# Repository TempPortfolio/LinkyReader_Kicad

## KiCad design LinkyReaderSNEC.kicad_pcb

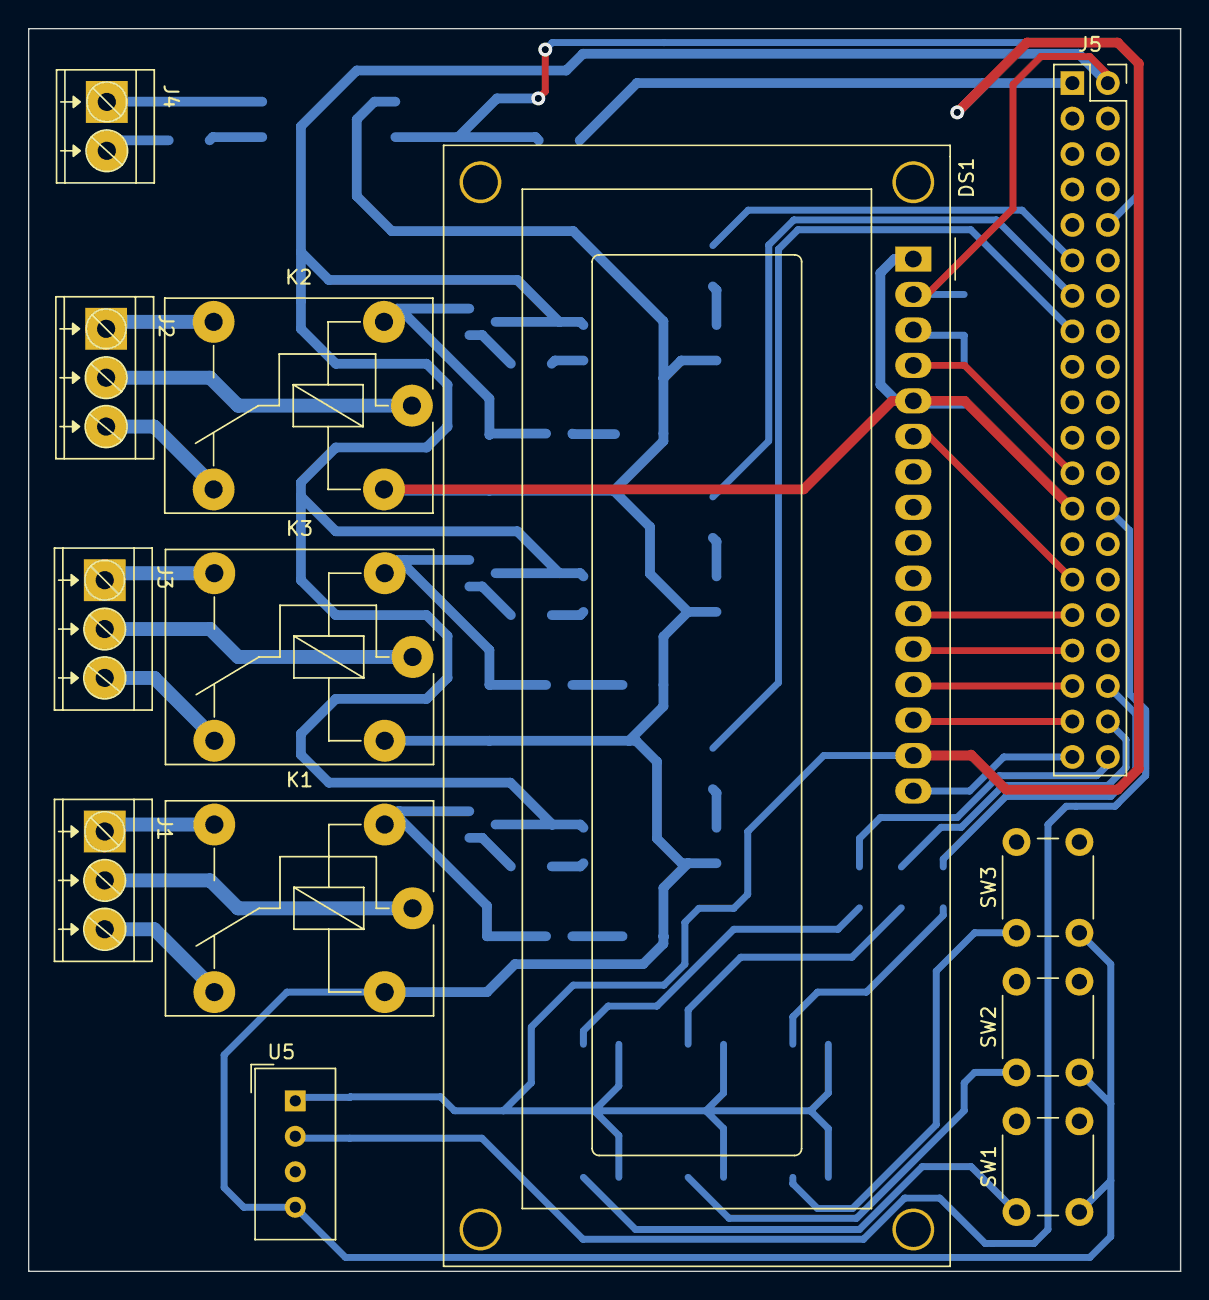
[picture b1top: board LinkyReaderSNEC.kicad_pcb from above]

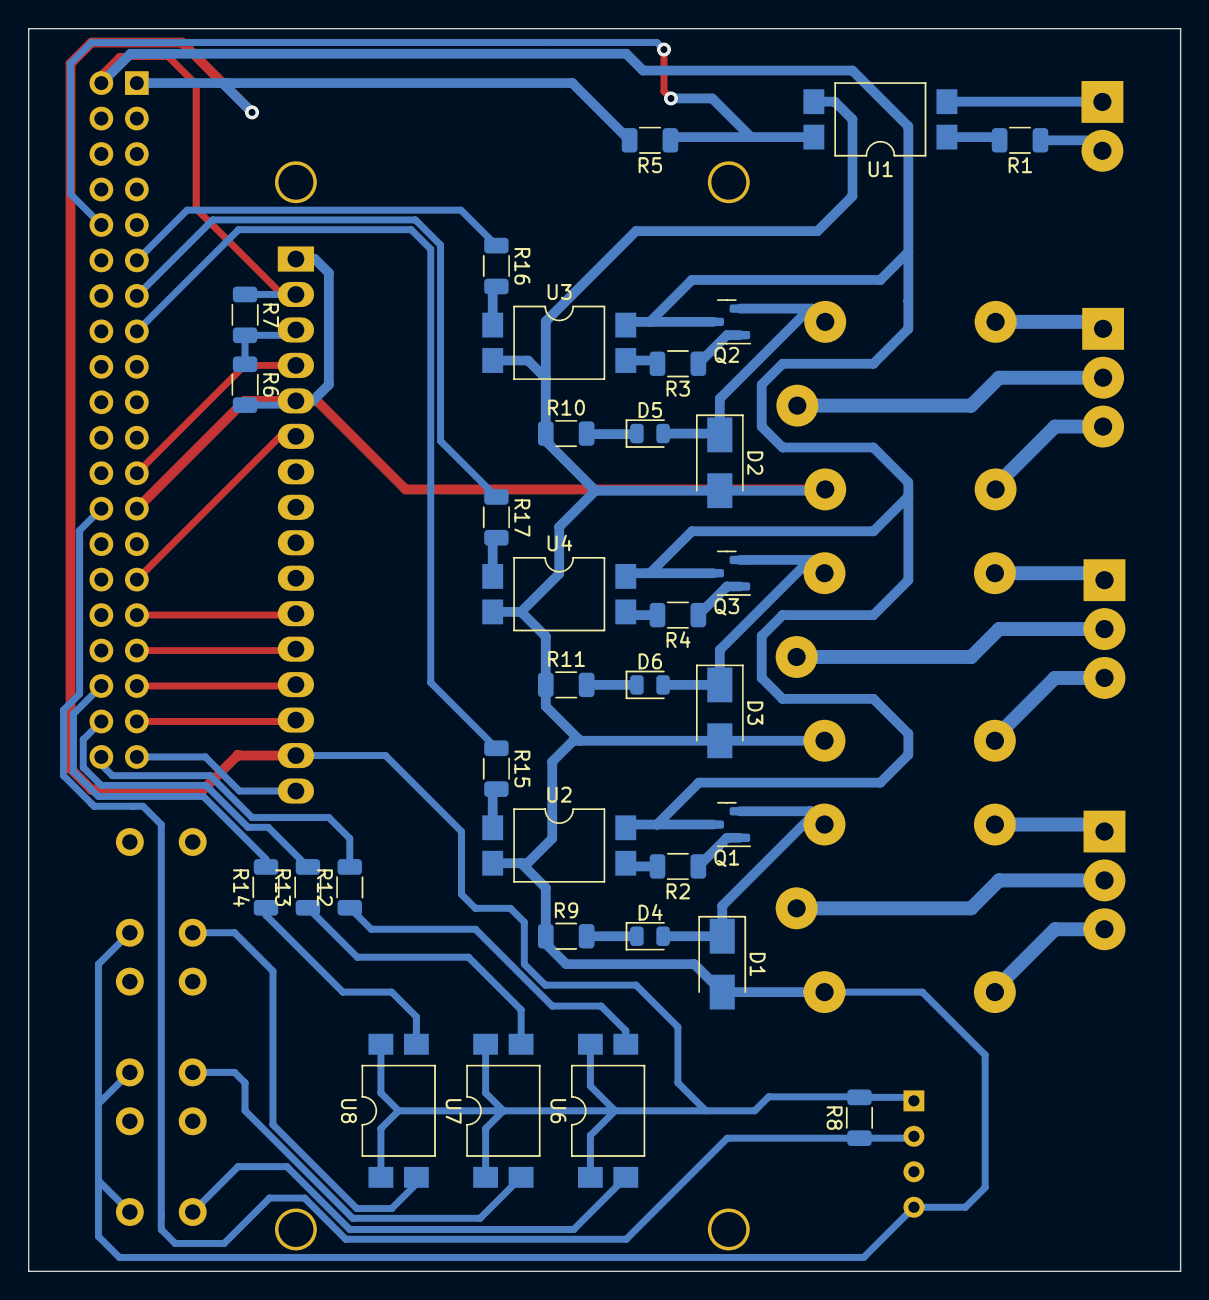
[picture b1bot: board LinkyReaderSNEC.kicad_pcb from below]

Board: 2 copper layers, 82.5 x 89.0 mm, 46 parts (33 on the bottom side), 52 nets.

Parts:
D1, D2, D3: D; D_SMA
D4, D5, D6: LED; LED_0805_2012Metric
DS1: WC1602A
J1, J2, J3: Screw_Terminal_01x03; terminal_x1_x3
J4: Screw_Terminal_01x02; terminal_x1_x2
J5: Conn_02x20_Odd_Even; PinSocket_2x20_P2.54mm_Vertical
K1, K2, K3: FINDER-36.11; Relay_SPDT_Finder_36.11
Q1, Q2, Q3: Q_NPN_BEC; SOT-23
R1, R2, R3, R4, R6, R7, R8: 1.2k; R_1206_3216Metric
R5, R9, R10, R11: 3.3k; R_1206_3216Metric
R12, R13, R14, R15, R16, R17: 220; R_1206_3216Metric
SW1, SW2, SW3: SW_DIP_x02; SW_PUSH_6mm_H5mm
U1, U2, U3, U4, U6, U7, U8: SFH6206-2T; SMDIP-4_W9.53mm_Clearance8mm
U5: DHT11; Aosong_DHT11_5.5x12.0_P2.54mm

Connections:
+3.3V: DS1.15 (LED(+)), J5.1, R5.2, R8.2, U5.1 (VCC), U6.1, U6.4, U7.1, U7.4, U8.1, U8.4
+5V: DS1.2 (VDD), J5.2, Q1.3 (C), Q2.3 (C), Q3.3 (C), R7.1, U2.4, U3.4, U4.4
GND: D1.2 (A), D2.2 (A), D3.2 (A), DS1.1 (VSS), DS1.5 (R/W), J5.25, K1.A2, K2.A2, K3.A2, R6.2, R9.1, R10.1, R11.1, SW1.2, SW2.2, SW3.2, U1.3, U2.2, U3.2, U4.2, U5.4 (GND)
unnamed: D1.1 (K), D4.2 (A), K1.A1, Q1.2 (E)
unnamed: D2.1 (K), D5.2 (A), K2.A1, Q2.2 (E)
unnamed: D3.1 (K), D6.2 (A), K3.A1, Q3.2 (E)
unnamed: D4.1 (K), R9.2
unnamed: D5.1 (K), R10.2
unnamed: D6.1 (K), R11.2
unnamed: DS1.3 (VO), R6.1, R7.2
unnamed: DS1.4 (RS), J5.23
unnamed: DS1.6 (E), J5.29
unnamed: DS1.11 (D4), J5.31
unnamed: DS1.12 (D5), J5.33
unnamed: DS1.13 (D6), J5.35
unnamed: DS1.14 (D7), J5.37
unnamed: DS1.16 (LED(-)), J5.39
unnamed: J1.1, K1.14
unnamed: J1.2, K1.11
unnamed: J1.3, K1.12
unnamed: J2.1, K2.14
unnamed: J2.2, K2.11
unnamed: J2.3, K2.12
unnamed: J3.1, K3.14
unnamed: J3.2, K3.11
unnamed: J3.3, K3.12
unnamed: J4.1, U1.2
unnamed: J4.2, R1.1
unnamed: J5.10, R5.1, U1.4
unnamed: J5.11, R16.1
unnamed: J5.13, R17.1
unnamed: J5.15, R15.1
unnamed: J5.26, R8.1, U5.2 (IO)
unnamed: J5.36, R14.2
unnamed: J5.38, R13.2
unnamed: J5.40, R12.2
unnamed: Q1.1 (B), R2.1
unnamed: Q2.1 (B), R3.1
unnamed: Q3.1 (B), R4.1
unnamed: R1.2, U1.1
unnamed: R2.2, U2.3
unnamed: R3.2, U3.3
unnamed: R4.2, U4.3
unnamed: SW1.1, U6.2
unnamed: SW2.1, U7.2
unnamed: SW3.1, U8.2
unnamed: R15.2, U2.1
unnamed: R16.2, U3.1
unnamed: R17.2, U4.1
unnamed: R12.1, U6.3
unnamed: R13.1, U7.3
unnamed: R14.1, U8.3

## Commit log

2024-08-27 init
2024-08-27 Add documentation
